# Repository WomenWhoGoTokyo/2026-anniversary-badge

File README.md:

# 2026-anniversary-badge

このリポジトリは Women Who Go Tokyo 10 周年記念バッジ (通称 `wwgt2026badge`) のファームウェア / 回路図 / 組み立てガイドをまとめたものです。
RP2040 Zero と TinyGo を組み合わせた、はんだ付けから始められるワークショップ向けキットです。

> ## Special Thanks
>
> 本ワークショップは [**TinyGo Keeb**](https://tinygo-keeb.org/) コミュニティの多大なご協力のもと制作しました。
> ベースとなった [tinygo-keeb/workshop-conf2025badge](https://github.com/tinygo-keeb/workshop-conf2025badge) を含む、
> サンプルコード・回路設計・ワークショップ運営等の惜しみない共有に、心より御礼申し上げます。

不明点は Issue で気軽に質問してください。

## このリポジトリの内容

- `src/` : TinyGo で書かれたサンプルファームウェア
- `wwgt2026badge/` : KiCad プロジェクト (回路図・PCB データ)
- `lib/` : 自作シンボル / フットプリントライブラリ
- `tools/imgconv/` : 液晶用 RGB565 画像の生成ツール
- `build/BUILD.md` : ハードウェアの組み立て手順

## 回路図

KiCanvas でブラウザから直接閲覧できます。

- [kiCanvas で開く](https://kicanvas.org/?repo=https%3A%2F%2Fgithub.com%2FWomenWhoGoTokyo%2F2026-anniversary-badge%2Ftree%2Fmain%2Fwwgt2026badge)

## ハードウェアの組み立て

はんだ付けの手順、組み立て順序、必要な工具などはビルドガイドにまとめています。

- [ビルドガイド](./build/BUILD.md)

# 環境設定

[TinyGo Keeb の環境設定](https://github.com/tinygo-keeb/workshop-conf2025badge#%E7%92%B0%E5%A2%83%E8%A8%AD%E5%AE%9A) をご確認ください。

# 開発対象

このバッジのマイコンは RP2040 (Cortex M0+) で、マイコンボードとして [Waveshare RP2040-Zero](https://www.waveshare.com/wiki/RP2040-Zero) を使用しています。TinyGo のターゲット名は `waveshare-rp2040-zero` です。

主な機能は次の通りです。

- Waveshare RP2040-Zero
- ST7789 液晶
- LED 付きロータリーエンコーダー
- アナログジョイスティック
- RGB LED 付きキースイッチ × 2
- ブザー
- Grove 端子

ピン配置の概要は次の通りです。詳細は回路図を参照してください。

| 機能 | ピン |
| ---- | ---- |
| 上ボタン | GPIO0 |
| 下ボタン | GPIO1 |
| ロータリーエンコーダー A / B | GPIO2 / GPIO3 |
| SK6812MINI-E (WS2812B 互換) | GPIO4 |
| エンコーダースイッチ | D5 (GPIO5) |
| エンコーダー LED | D7 (GPIO7) |
| ブザー | D8 (GPIO8) PWM4 |
| ST7789 RST / DC / CS / BL | GPIO9 / GPIO12 / GPIO13 / GPIO14 |
| ジョイスティック X / Y | GPIO29 / GPIO28 (ADC) |

# サンプルファームウェアの実行

最初にこのリポジトリを clone してください。以降のコマンドはリポジトリのルートから実行します。

```
$ git clone https://github.com/WomenWhoGoTokyo/2026-anniversary-badge
$ cd 2026-anniversary-badge
```

サンプルは `src/` 以下に 1 ファイル 1 機能のフラットな構成で置いてあります。複数のファイルがそれぞれ `package main` を持っているため、ビルドするときはディレクトリではなく **ファイルを直接指定** します。

```
$ tinygo build -o out.uf2 --target waveshare-rp2040-zero --size short ./src/blink.go
```

## ビルド + 書き込み (ブートローダー経由)

RP2040 Zero の `BOOT` ボタンを押しながら `RESET` ボタンを押す (または USB を抜き差しする) と、ブートローダーが起動して PC から外付けドライブとして見えます。あとは `*.uf2` ファイルを D&D でコピーすれば書き込み完了です。

この方式は TinyGo 以外で作られた uf2 にも使えるので、最初に動作確認したいときに便利です。

## ビルド + 書き込み (tinygo flash)

`tinygo flash` を使えば、ビルドと書き込みを一度に実行できます。エラーメッセージが出なければ成功です。

```
$ tinygo flash --target waveshare-rp2040-zero --size short ./src/blink.go
```

シリアル出力の確認は `tinygo monitor` を使います。ポートを自動検出できない場合は `--port` で明示指定してください。

```
$ tinygo ports
Port                 ID        Boards
COM7                 2E8A:000A waveshare-rp2040-zero

$ tinygo monitor --port COM7
```

`tinygo flash --monitor` でまとめて実行することもできますが、環境によってはポートを誤判定するので、うまく動かないときは別々に実行してください。

# サンプル一覧

`src/` には次のサンプルが入っています。それぞれ `tinygo flash --target waveshare-rp2040-zero ./src/<ファイル名>` で書き込めます。

| ファイル | 内容                                 |
| -------- |------------------------------------|
| `blink.go` | ロータリーエンコーダー LED の点滅                |
| `sk6812.go` | キースイッチ下の RGB LED を順番に光らせる          |
| `key_input.go` | 上下キーの押下検出                          |
| `rotary.go` | ロータリーエンコーダーの回転値取得                  |
| `encorder_sw.go` | ロータリーエンコーダー押下の検出                   |
| `joystick.go` | アナログジョイスティックの XY 値取得               |
| `st7789_txt.go` | ST7789 液晶へのテキスト表示                  |
| `buzzer.go` | ブザーでドレミファソラシドを鳴らす                  |
| `all.go` | 全機能を統合したデモ (ロゴ表示 + 入力連動 LED + ブザー) |

## L チカ (blink.go)

ロータリーエンコーダー LED (D7) を 1 秒間隔で点滅させます。

```
$ tinygo flash --target waveshare-rp2040-zero --size short ./src/blink.go
```

LED が光ったら成功です。`time.Sleep` の値を変えて点滅速度を調整してみましょう。

## RGB LED (sk6812.go)

基板上の SK6812MINI-E は 2 個搭載されています。`WriteRaw([]uint32{...})` で複数の LED を一度に制御できます。

```
$ tinygo flash --target waveshare-rp2040-zero --size short ./src/sk6812.go
```

色は uint32 で指定し、最上位から 8bit ずつ Green / Red / Blue / (SK6812 RGBW の場合 White) を表します。

```go
colors := []uint32{
    0xFFFFFFFF, // white
    0xFF0000FF, // green
    0x00FF00FF, // red
    0x0000FFFF, // blue
}
```

## キー入力 (key_input.go)

上下 2 キーをマイコンの GPIO 入力で読み取ります。プルアップにしているので、押下時に Low になります。

```
$ tinygo flash --target waveshare-rp2040-zero --size short ./src/key_input.go
$ tinygo monitor
上側のボタンが押されました
下側のボタンが押されました
```

## ロータリーエンコーダー (rotary.go)

`tinygo.org/x/drivers/encoders` の Quadrature ドライバを使います。

```
$ tinygo flash --target waveshare-rp2040-zero --size short ./src/rotary.go
$ tinygo monitor
value:  -1
value:  0
value:  1
```

## エンコーダースイッチ (encorder_sw.go)

ロータリーエンコーダーは押し込むとボタンとしても動作します。GPIO5 を Low 検出するだけです。

```
$ tinygo flash --target waveshare-rp2040-zero --size short ./src/encorder_sw.go
$ tinygo monitor
encorder sw is pressed!!
```

## アナログジョイスティック (joystick.go)

XY の二軸を ADC で読み取り、16 進数で表示します。何もしていない時は `0x8000` 付近の値が表示されます。

```
$ tinygo flash --target waveshare-rp2040-zero --size short ./src/joystick.go
$ tinygo monitor
8000 8000
6E10 7E10
```

## 液晶 (st7789_txt.go)

`tinygo.org/x/drivers/st7789` と `tinygo.org/x/tinyfont` を組み合わせて、の液晶に文字を表示します。

```
$ tinygo flash --target waveshare-rp2040-zero --size short ./src/st7789_txt.go
```

書き込みに成功すると "Hello / Gophers!" の文字が表示されます。

画像を表示したい場合は、`tools/imgconv` で PNG を RGB565 形式に変換し、`go:embed` で埋め込みます。

```
$ go run ./tools/imgconv -in src/images/badge240.png -out src/images/badge.rgb565
```

## ブザー (buzzer.go)

GPIO トグルでブザーを鳴らし、ドレミファソラシドを再生します。

```
$ tinygo flash --target waveshare-rp2040-zero --size short ./src/buzzer.go
```

`all.go` では PWM を使った実装になっています。長時間鳴らし続ける用途では PWM 方式の方が CPU 負荷を抑えられます。

## 全機能デモ (all.go)

液晶のロゴ表示、入力連動の RGB LED、ジョイスティック方向に応じた虹色表示、エンコーダー押下でブザー ON / OFF、エンコーダー回転で液晶を回転、といった全部入りのデモです。

```
$ tinygo flash --target waveshare-rp2040-zero --size short ./src/all.go
```

# 参考リンク

- [tinygo-keeb/workshop-conf2025badge](https://github.com/tinygo-keeb/workshop-conf2025badge) — 本リポジトリのベースとなったワークショップ
- [sago35/tinygo-keyboard を用いて自作キーボードを作ろう](https://qiita.com/sago35/items/b008ed03cd403742e7aa)
- [koebiten — TinyGo 向け 2D ゲームエンジン](https://github.com/sago35/koebiten)
- [基礎から学ぶ TinyGo の組込み開発](https://sago35.hatenablog.com/entry/2022/11/04/230919)

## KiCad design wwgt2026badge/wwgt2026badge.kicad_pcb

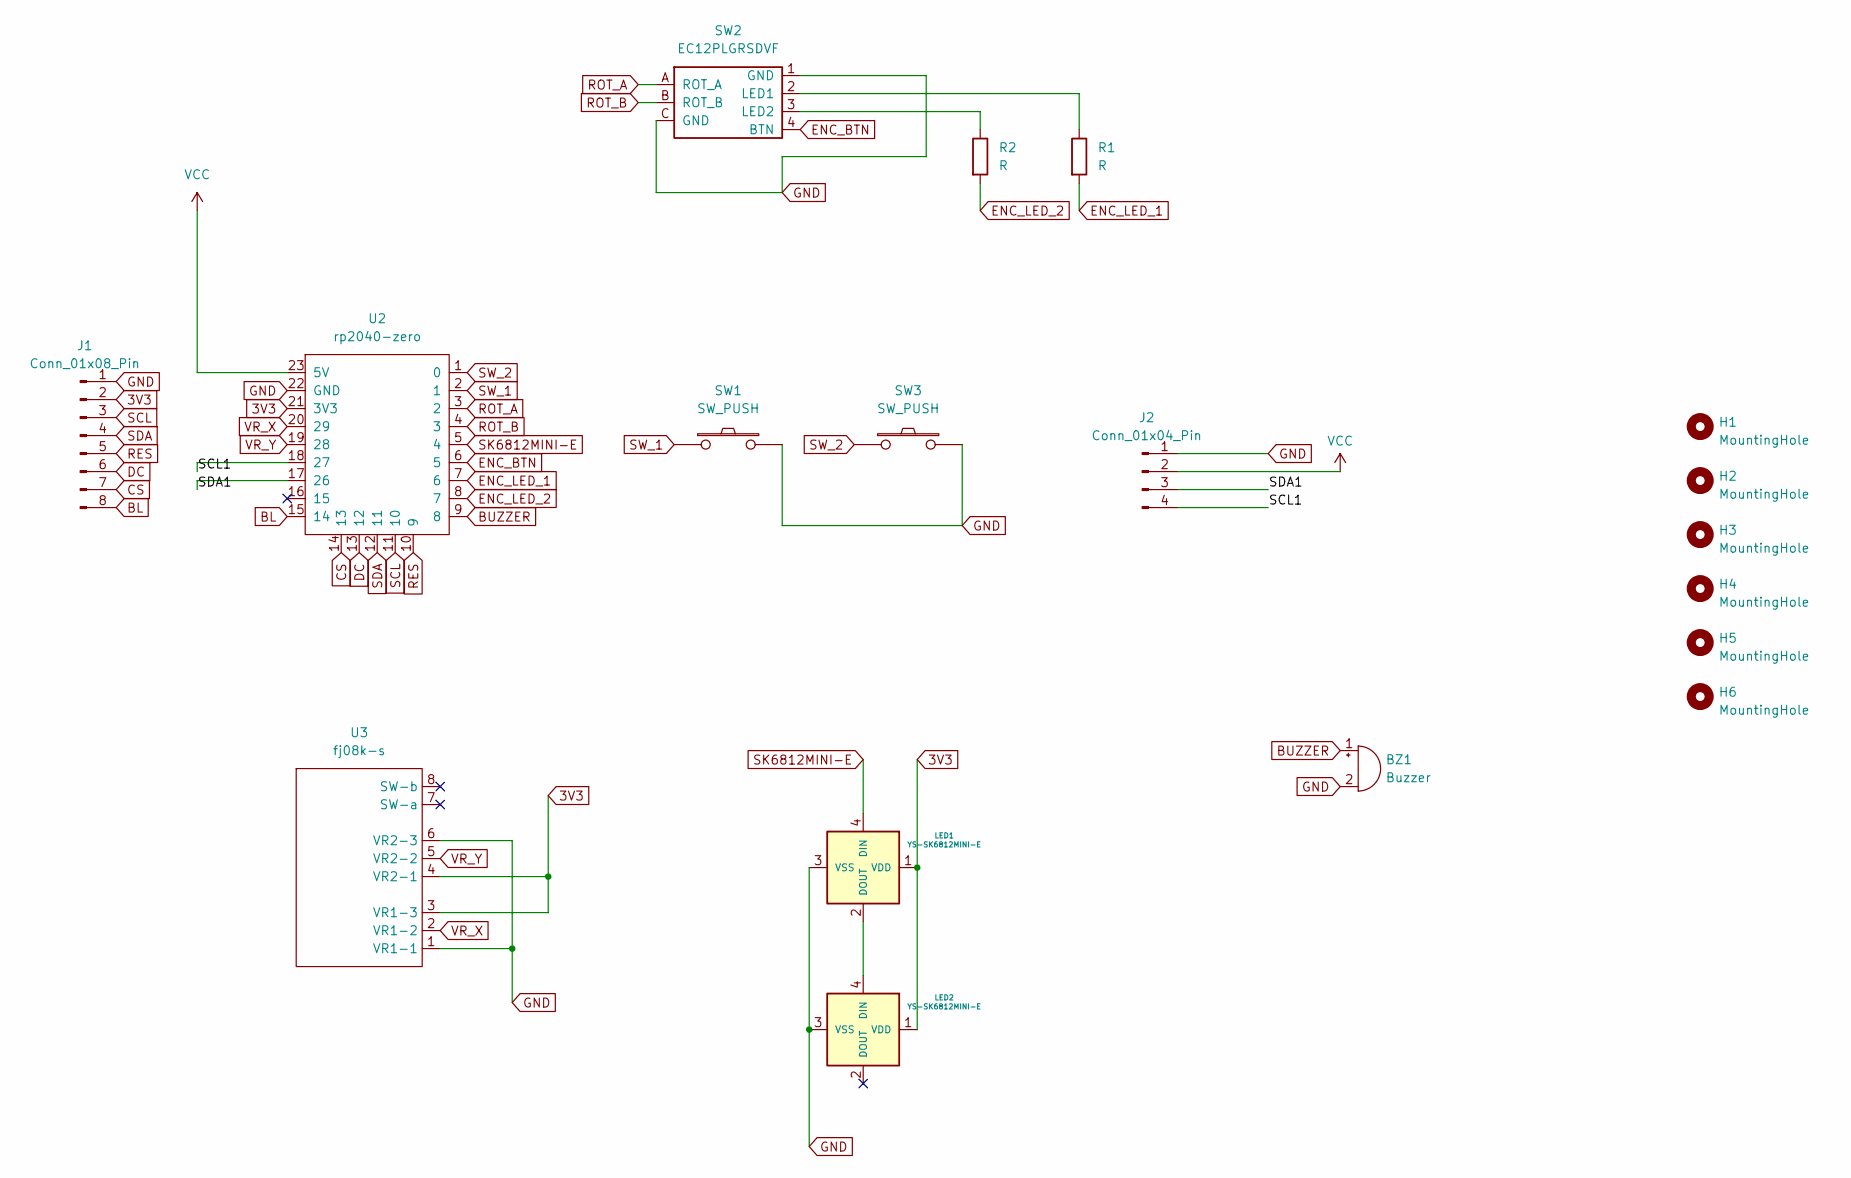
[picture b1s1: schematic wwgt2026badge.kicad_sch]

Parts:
BZ1: Buzzer; buzzer 5.5mm
H1, H2, H3, H4, H5, H6: MountingHole; M2_HOLE_v2
J1: Conn_01x08_Pin; PinHeader_1x08_P2.54mm_Vertical
J2: Conn_01x04_Pin; PinHeader_1x04_P2.00mm_Vertical
LED1, LED2: YS-SK6812MINI-E
R1, R2: R; R_Axial_DIN0207_L6.3mm_D2.5mm_P7.62mm_Horizontal
SW1, SW3: SW_PUSH; CherryMX_Hotswap
SW2: EC12PLGRSDVF; RotaryEncoder_Alps_EC12E-Switch_Vertical_H20mm_LED
U2: rp2040-zero
U3: fj08k-s; FJ08K-S

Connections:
3V3: J1.2, LED1.1 (VDD), LED2.1 (VDD), U2.21 (3V3), U3.3 (VR1-3), U3.4 (VR2-1)
/SCL1: J2.4, U2.18 (27)
/SDA1: J2.3, U2.17 (26)
BL: J1.8, U2.15 (14)
BUZZER: BZ1.1 (+), U2.9 (8)
CS: J1.7, U2.14 (13)
DC: J1.6, U2.13 (12)
ENC_BTN: SW2.4 (BTN), U2.6 (5)
ENC_LED_1: R1.2, U2.7 (6)
ENC_LED_2: R2.2, U2.8 (7)
GND: BZ1.2 (-), J1.1, J2.1, LED1.3 (VSS), LED2.3 (VSS), SW1.2, SW2.1 (GND), SW2.C (GND), SW3.2, U2.22 (GND), U3.1 (VR1-1), U3.6 (VR2-3)
unnamed: LED1.2 (DOUT), LED2.4 (DIN)
unnamed: R1.1, SW2.2 (LED1)
unnamed: R2.1, SW2.3 (LED2)
RES: J1.5, U2.10 (9)
ROT_A: SW2.A (ROT_A), U2.3 (2)
ROT_B: SW2.B (ROT_B), U2.4 (3)
SCL: J1.3, U2.11 (10)
SDA: J1.4, U2.12 (11)
SK6812MINI-E: LED1.4 (DIN), U2.5 (4)
SW_1: SW1.1, U2.2 (1)
SW_2: SW3.1, U2.1 (0)
VCC: J2.2, U2.23 (5V)
VR_X: U2.20 (29), U3.2 (VR1-2)
VR_Y: U2.19 (28), U3.5 (VR2-2)

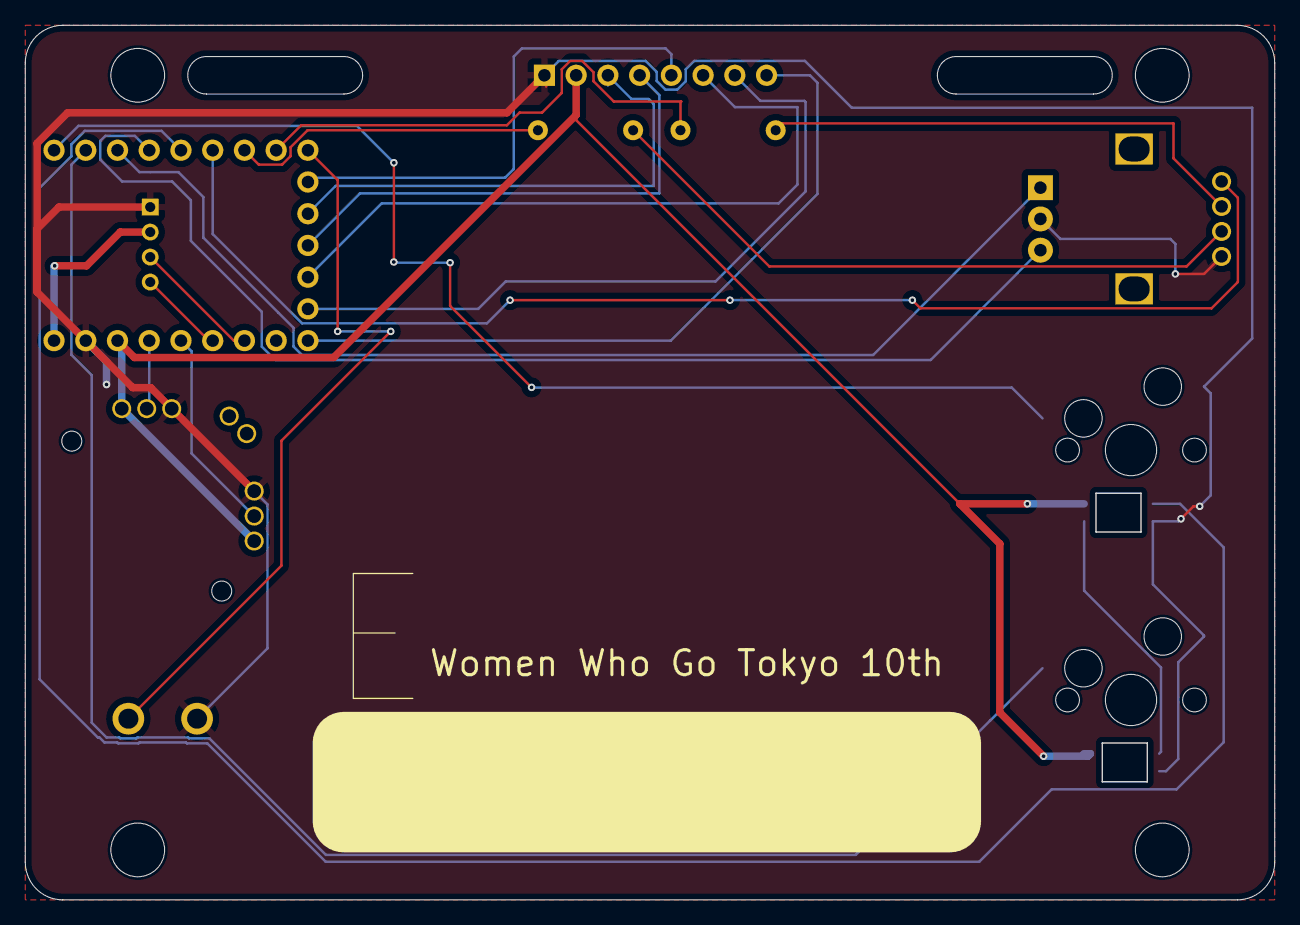
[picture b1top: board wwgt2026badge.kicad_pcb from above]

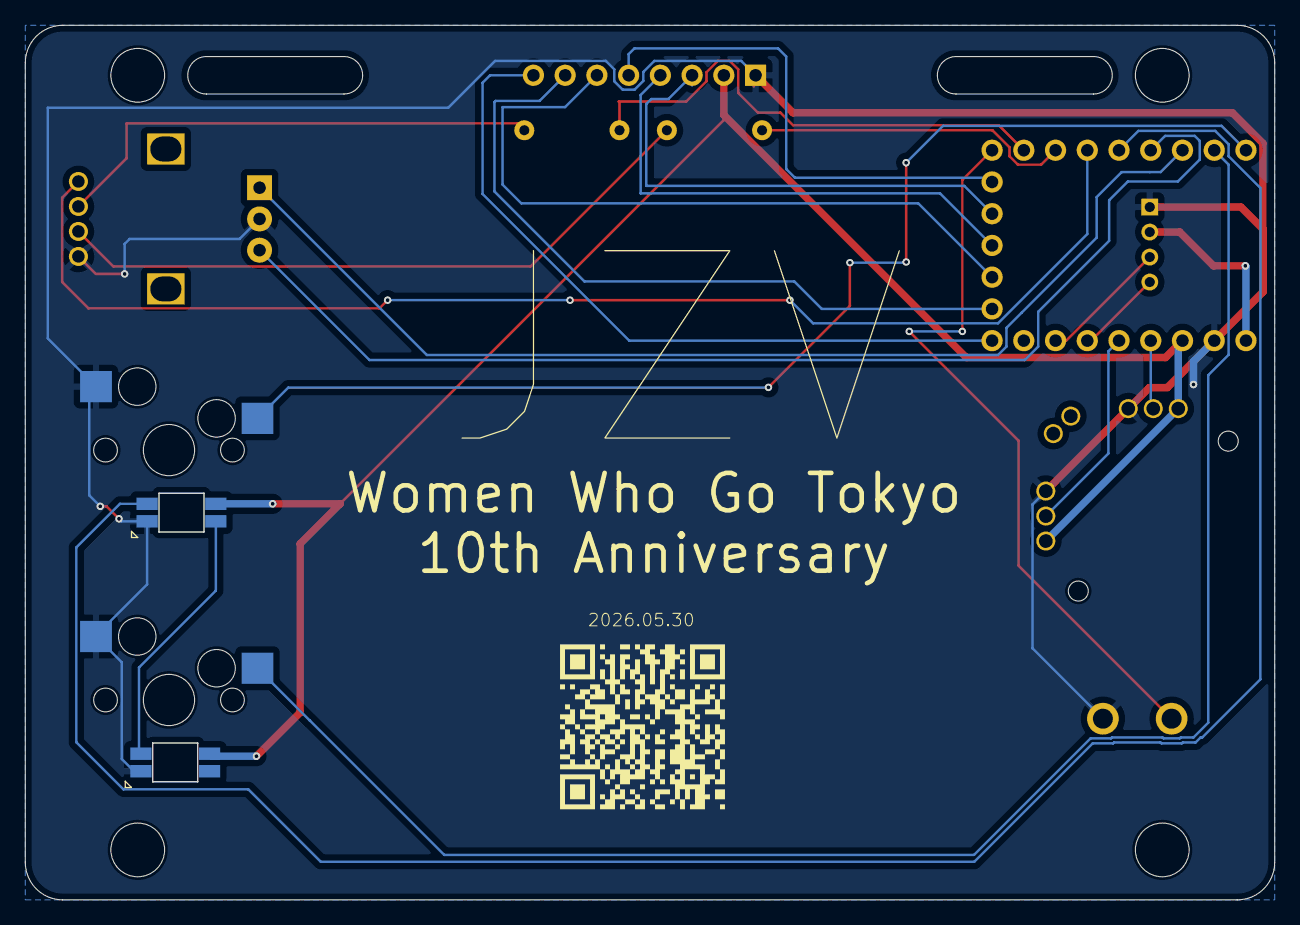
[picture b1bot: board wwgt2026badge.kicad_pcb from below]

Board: 2 copper layers, 100.0 x 70.0 mm, 19 parts (3 on the bottom side), 25 nets.

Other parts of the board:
qr-0.4: https://github.com/WomenWhoGoTokyo/2026-anniversa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; qr-0.4

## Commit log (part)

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2026-04-05 Add README.md
2026-04-06 エンコーダーのフットプリントを修正 + 回路およびPCBのエラーを修正
2026-04-06 QR コードを追加
2026-04-06 テスト用に QR コードを追加
2026-04-07 Grove端子の位置を調整してベタGNDを追加
2026-04-07 updated gopher font & gerbar files
2026-04-18 add sample code
2026-04-20 fixed pcb file
2026-04-21 fixed pcb file (front)
2026-04-21 added gbr files
2026-05-05 added sample code
2026-05-05 fixed
